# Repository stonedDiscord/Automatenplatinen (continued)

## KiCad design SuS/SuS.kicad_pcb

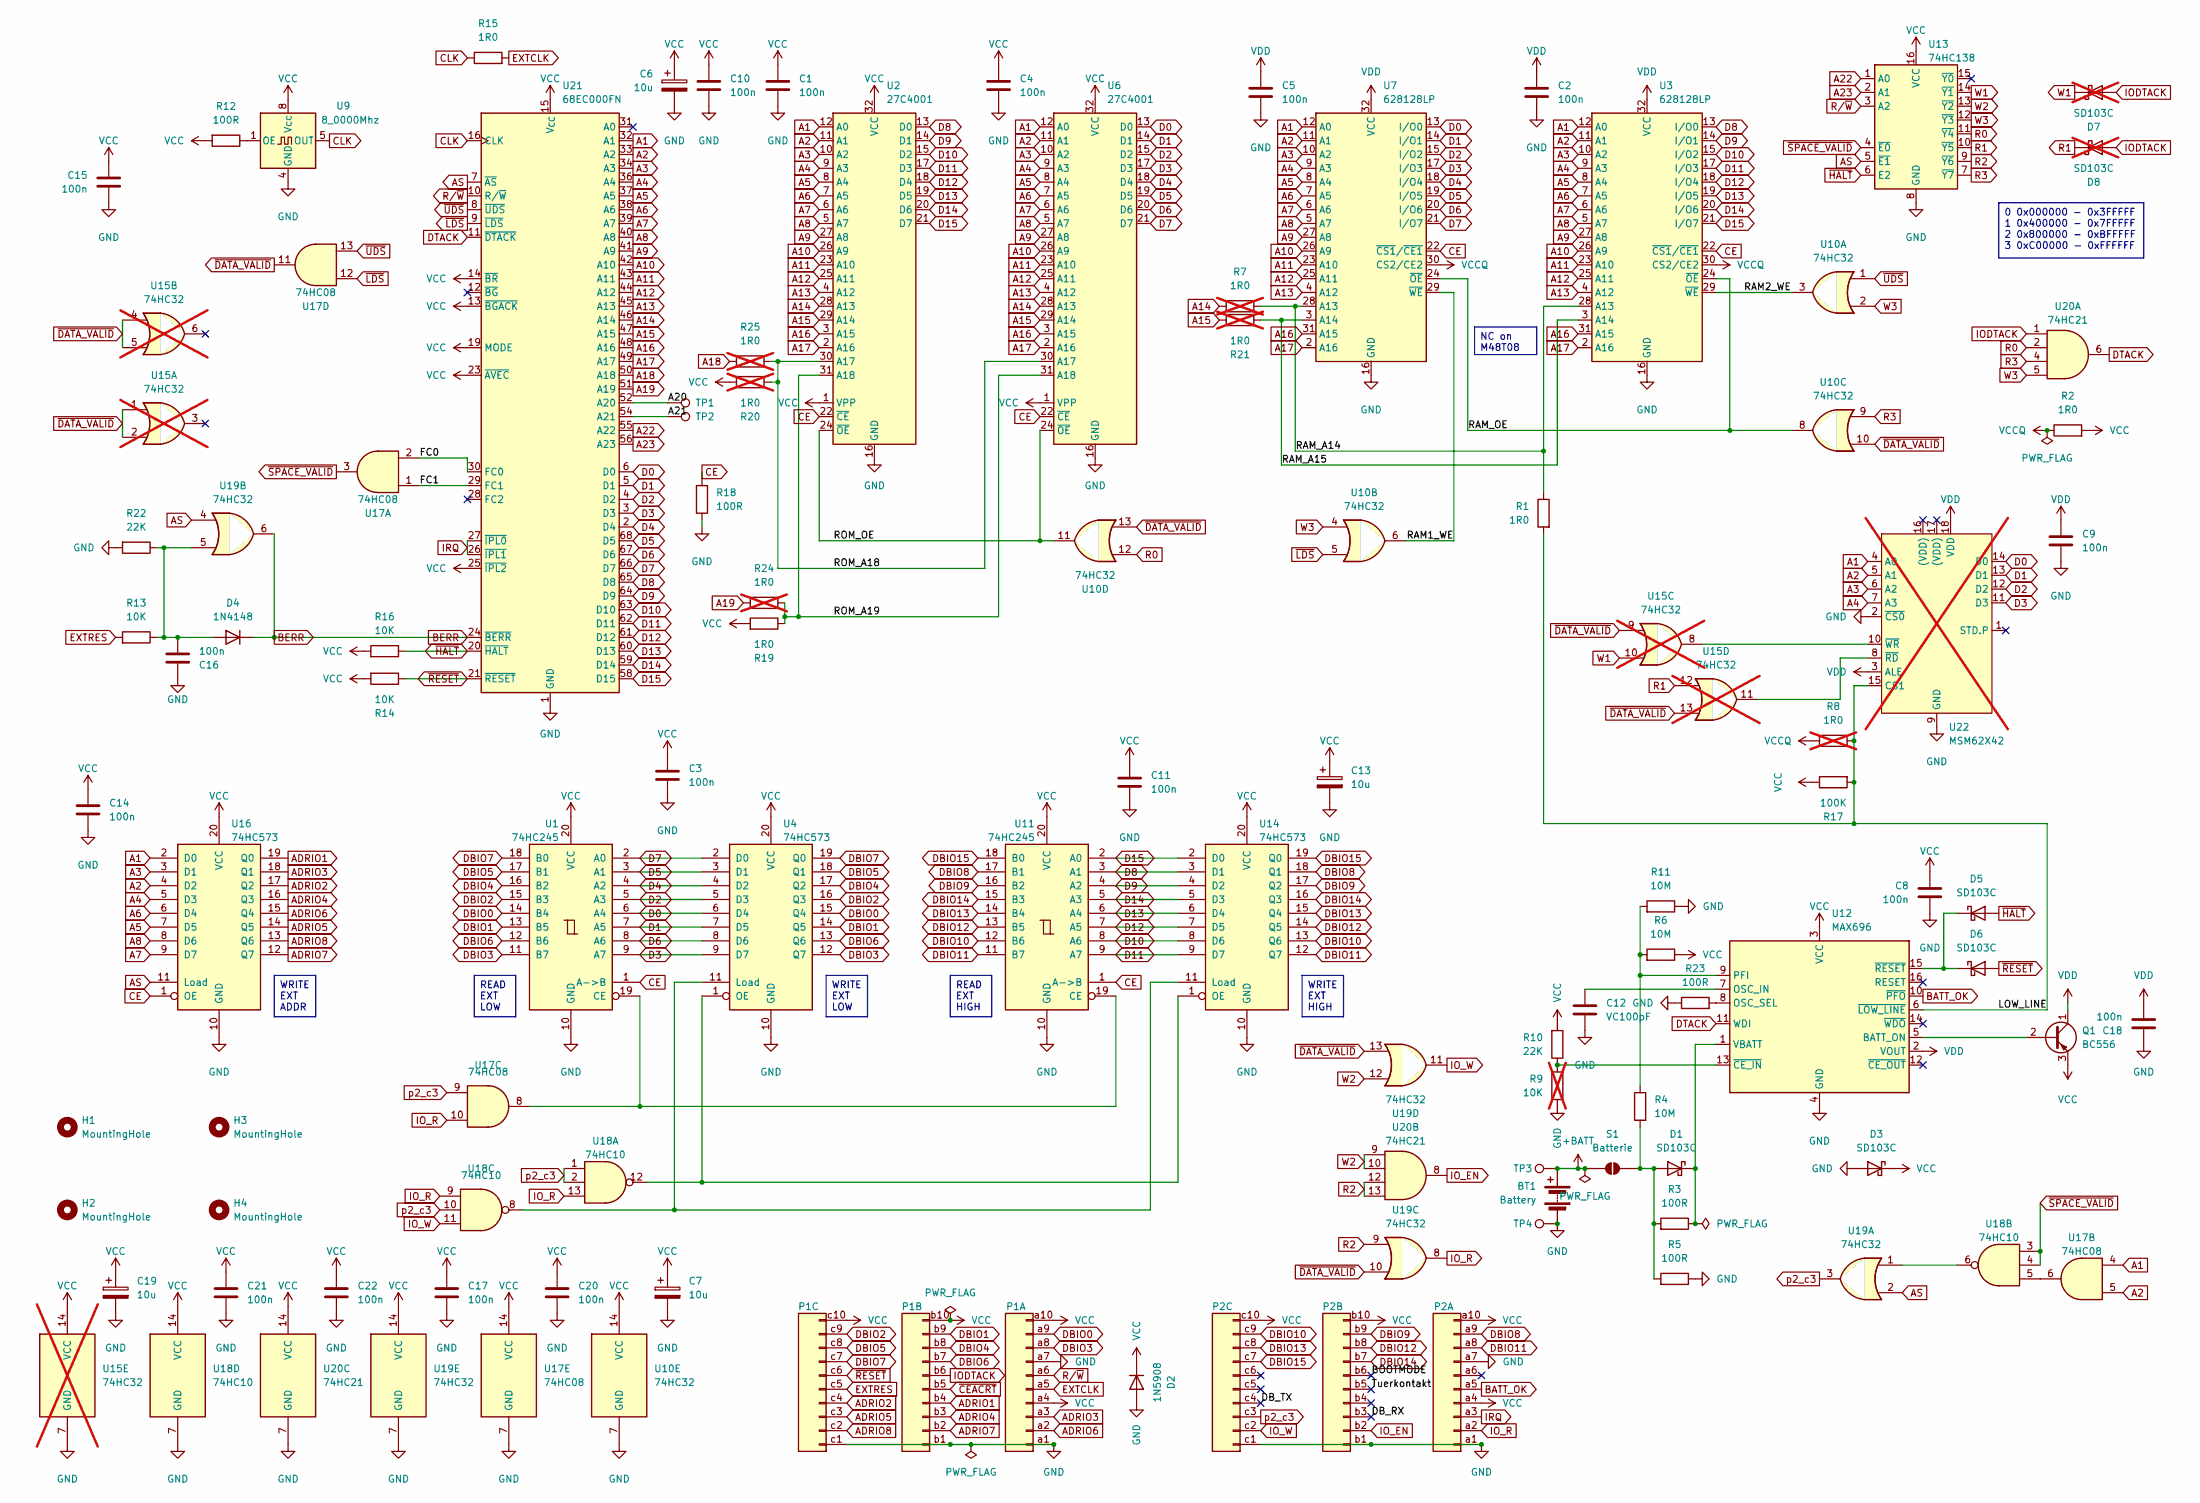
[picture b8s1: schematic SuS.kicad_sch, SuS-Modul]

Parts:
BT1: Battery; REPM1000
C1, C2, C3, C4, C5, C8, C9, C10, C11, C14, C15, C16, C17, C18, C20, C21, C22: 100n; C_Axial_L3.8mm_D2.6mm_P7.50mm_Horizontal
C6, C7, C13, C19: 10u; CP_Radial_Tantal_D5.0mm_P2.50mm
C12: VC100pF; C_Axial_L3.8mm_D2.6mm_P7.50mm_Horizontal
D1, D3, D5, D6: SD103C; D_DO-34_SOD68_P7.62mm_Horizontal
D2: 1N5908; D_DO-27_P15.24mm_Horizontal
D4: 1N4148; D_DO-35_SOD27_P7.62mm_Horizontal
D7, D8: SD103C; D_DO-34_SOD68_P7.62mm_Horizontal; not fitted
H1, H2: MountingHole; MountingHole_3mm
H3, H4: MountingHole; MountingHole_2.1mm
P1, P2: DIN41612_03x10_ABC; DIN41612_R3_3x10_Male_Vertical_THT
Q1: BC556; TO-92
R1, R2, R15, R19: 1R0; R_Axial_DIN0207_L6.3mm_D2.5mm_P10.16mm_Horizontal
R3, R5, R12, R18, R23: 100R; R_Axial_DIN0207_L6.3mm_D2.5mm_P10.16mm_Horizontal
R4, R6, R11: 10M; R_Axial_DIN0207_L6.3mm_D2.5mm_P10.16mm_Horizontal
R7, R8, R20, R21, R24, R25: 1R0; R_Axial_DIN0207_L6.3mm_D2.5mm_P10.16mm_Horizontal; not fitted
R9: 10K; R_Axial_DIN0207_L6.3mm_D2.5mm_P10.16mm_Horizontal; not fitted
R10, R22: 22K; R_Axial_DIN0207_L6.3mm_D2.5mm_P10.16mm_Horizontal
R13, R14, R16: 10K; R_Axial_DIN0207_L6.3mm_D2.5mm_P10.16mm_Horizontal
R17: 100K; R_Axial_DIN0207_L6.3mm_D2.5mm_P10.16mm_Horizontal
S1: Batterie; SolderJumper-2_P1.3mm_Open_Pad1.0x1.5mm
TP1, TP2: TestPoint; TestPoint_THTPad_D1.0mm_Drill0.5mm
TP3, TP4: TestPoint; TestPoint_THTPad_D2.0mm_Drill1.0mm
U1, U11: 74HC245; DIP-20_W7.62mm
U2, U6: 27C4001; DIP-32_W15.24mm_Socket
U3, U7: 628128LP; DIP-32_W15.24mm
U4, U14, U16: 74HC573; DIP-20_W7.62mm
U9: 8_0000Mhz; Oscillator_SeikoEpson_SG-8002DC
U10, U19: 74HC32; DIP-14_W7.62mm
U12: MAX696; DIP-16_W7.62mm
U13: 74HC138; DIP-16_W7.62mm
U15: 74HC32; DIP-14_W7.62mm; not fitted
U17: 74HC08; DIP-14_W7.62mm
U18: 74HC10; DIP-14_W7.62mm
U20: 74HC21; DIP-14_W7.62mm
U21: 68EC000FN; PLCC-68_THT-Socket
U22: MSM62X42; DIP-18_W7.62mm; not fitted

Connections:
+BATT: BT1.1 (+), S1.2 (B), TP3.1 (1_1)
/A20: TP1.1 (1_1), U21.52 (A20)
/A21: TP2.1 (1_1), U21.54 (A21)
/BOOTMODE: P2.b6
/DB_RX: P2.b3
/DB_TX: P2.c4
/FC0: U17.2, U21.30 (FC0)
/FC1: U17.1, U21.29 (FC1)
/LOW_LINE: R1.2, R8.1, R17.2, U12.6 (~LOW_LINE), U22.15 (CS1)
/RAM1_WE: U7.29 (~WE), U10.6
/RAM2_WE: U3.29 (~WE), U10.3
/RAM_A14: R1.1, R7.2, U3.28 (A13), U7.28 (A13)
/RAM_A15: R21.2, U3.3 (A14), U7.3 (A14)
/RAM_OE: U3.24 (~OE), U7.24 (~OE), U10.8
/ROM_A18: R20.1, R25.2, U2.30 (A17), U6.30 (A17)
/ROM_A19: R19.1, R24.2, U2.31 (A18), U6.31 (A18)
/ROM_OE: U2.24 (~OE), U6.24 (~OE), U10.11
/Tuerkontakt: P2.b5
A1: U2.12 (A0), U3.12 (A0), U6.12 (A0), U7.12 (A0), U16.2 (D0), U17.4, U21.32 (A1), U22.4 (A0)
A2: U2.11 (A1), U3.11 (A1), U6.11 (A1), U7.11 (A1), U16.4 (D2), U17.5, U21.33 (A2), U22.5 (A1)
A3: U2.10 (A2), U3.10 (A2), U6.10 (A2), U7.10 (A2), U16.3 (D1), U21.34 (A3), U22.6 (A2)
A4: U2.9 (A3), U3.9 (A3), U6.9 (A3), U7.9 (A3), U16.5 (D3), U21.36 (A4), U22.7 (A3)
A5: U2.8 (A4), U3.8 (A4), U6.8 (A4), U7.8 (A4), U16.7 (D5), U21.37 (A5)
A6: U2.7 (A5), U3.7 (A5), U6.7 (A5), U7.7 (A5), U16.6 (D4), U21.38 (A6)
A7: U2.6 (A6), U3.6 (A6), U6.6 (A6), U7.6 (A6), U16.9 (D7), U21.39 (A7)
A8: U2.5 (A7), U3.5 (A7), U6.5 (A7), U7.5 (A7), U16.8 (D6), U21.40 (A8)
A9: U2.27 (A8), U3.27 (A8), U6.27 (A8), U7.27 (A8), U21.41 (A9)
A10: U2.26 (A9), U3.26 (A9), U6.26 (A9), U7.26 (A9), U21.42 (A10)
A11: U2.23 (A10), U3.23 (A10), U6.23 (A10), U7.23 (A10), U21.43 (A11)
A12: U2.25 (A11), U3.25 (A11), U6.25 (A11), U7.25 (A11), U21.44 (A12)
A13: U2.4 (A12), U3.4 (A12), U6.4 (A12), U7.4 (A12), U21.45 (A13)
A14: R7.1, U2.28 (A13), U6.28 (A13), U21.46 (A14)
A15: R21.1, U2.29 (A14), U6.29 (A14), U21.47 (A15)
A16: U2.3 (A15), U3.31 (A15), U6.3 (A15), U7.31 (A15), U21.48 (A16)
A17: U2.2 (A16), U3.2 (A16), U6.2 (A16), U7.2 (A16), U21.49 (A17)
A18: R25.1, U21.50 (A18)
A19: R24.1, U21.51 (A19)
A22: U13.1 (A0), U21.55 (A22)
A23: U13.2 (A1), U21.56 (A23)
ADRIO1: P1.b4, U16.19 (Q0)
ADRIO2: P1.c4, U16.17 (Q2)
ADRIO3: P1.a3, U16.18 (Q1)
ADRIO4: P1.b3, U16.16 (Q3)
ADRIO5: P1.c3, U16.14 (Q5)
ADRIO6: P1.a2, U16.15 (Q4)
ADRIO7: P1.b2, U16.12 (Q7)
ADRIO8: P1.c2, U16.13 (Q6)
AS: U13.5 (~E1), U16.11 (Load), U19.2, U19.4, U21.7 (~AS)
BATT_OK: P2.a5, U12.10 (~PFO)
BERR: D4.1 (K), U19.6, U21.24 (~BERR)
CE: R18.2, U1.1 (A->B), U2.22 (~CE), U3.22 (~CS1/~CE1), U6.22 (~CE), U7.22 (~CS1/~CE1), U11.1 (A->B), U16.1 (OE)
CLK: R15.1, U9.5 (OUT), U21.16 (CLK)
CLOCKOUT: P1.a5, R15.2
D0: U1.6 (A4), U4.6 (D4), U6.13 (D0), U7.13 (I/O0), U21.6 (D0), U22.14 (D0)
D1: U1.7 (A5), U4.7 (D5), U6.14 (D1), U7.14 (I/O1), U21.5 (D1), U22.13 (D1)
D2: U1.5 (A3), U4.5 (D3), U6.15 (D2), U7.15 (I/O2), U21.4 (D2), U22.12 (D2)
D3: U1.9 (A7), U4.9 (D7), U6.17 (D3), U7.17 (I/O3), U21.3 (D3), U22.11 (D3)
D4: U1.4 (A2), U4.4 (D2), U6.18 (D4), U7.18 (I/O4), U21.2 (D4)
D5: U1.3 (A1), U4.3 (D1), U6.19 (D5), U7.19 (I/O5), U21.68 (D5)
D6: U1.8 (A6), U4.8 (D6), U6.20 (D6), U7.20 (I/O6), U21.67 (D6)
D7: U1.2 (A0), U4.2 (D0), U6.21 (D7), U7.21 (I/O7), U21.66 (D7)
D8: U2.13 (D0), U3.13 (I/O0), U11.3 (A1), U14.3 (D1), U21.65 (D8)
D9: U2.14 (D1), U3.14 (I/O1), U11.4 (A2), U14.4 (D2), U21.64 (D9)
D10: U2.15 (D2), U3.15 (I/O2), U11.8 (A6), U14.8 (D6), U21.63 (D10)
D11: U2.17 (D3), U3.17 (I/O3), U11.9 (A7), U14.9 (D7), U21.62 (D11)
D12: U2.18 (D4), U3.18 (I/O4), U11.7 (A5), U14.7 (D5), U21.61 (D12)
D13: U2.19 (D5), U3.19 (I/O5), U11.6 (A4), U14.6 (D4), U21.60 (D13)
D14: U2.20 (D6), U3.20 (I/O6), U11.5 (A3), U14.5 (D3), U21.59 (D14)
D15: U2.21 (D7), U3.21 (I/O7), U11.2 (A0), U14.2 (D0), U21.58 (D15)
DBIO0: P1.a9, U1.14 (B4), U4.15 (Q4)
DBIO1: P1.b9, U1.13 (B5), U4.14 (Q5)
DBIO2: P1.c9, U1.15 (B3), U4.16 (Q3)
DBIO3: P1.a8, U1.11 (B7), U4.12 (Q7)
DBIO4: P1.b8, U1.16 (B2), U4.17 (Q2)
DBIO5: P1.c8, U1.17 (B1), U4.18 (Q1)
DBIO6: P1.b7, U1.12 (B6), U4.13 (Q6)
DBIO7: P1.c7, U1.18 (B0), U4.19 (Q0)
DBIO8: P2.a9, U11.17 (B1), U14.18 (Q1)
DBIO9: P2.b9, U11.16 (B2), U14.17 (Q2)
DBIO10: P2.c9, U11.12 (B6), U14.13 (Q6)
DBIO11: P2.a8, U11.11 (B7), U14.12 (Q7)
DBIO12: P2.b8, U11.13 (B5), U14.14 (Q5)
DBIO13: P2.c8, U11.14 (B4), U14.15 (Q4)
DBIO14: P2.b7, U11.15 (B3), U14.16 (Q3)
DBIO15: P2.c7, U11.18 (B0), U14.19 (Q0)
DTACK: U12.11 (WDI), U20.6, U21.11 (~DTACK)
GND: BT1.2 (-), C1.2, C2.2, C3.2, C4.2, C5.2, C6.2, C7.2, C8.2, C9.2, C10.2, C11.2, C12.2, C13.2, C14.2, C15.2, C16.1, C17.2, C18.1, C19.2, C20.2, C21.2, C22.2, D2.2 (A), D3.2 (A), P1.a1, P1.a7, P1.b1, P1.c1, P2.a1, P2.a7, P2.b1, P2.c1, R5.1, R9.1, R11.1, R18.1, R22.2, R23.1, TP4.1 (1_1), U1.10 (GND), U2.16 (GND), U3.16 (GND), U4.10 (GND), U6.16 (GND), U7.16 (GND), U9.4 (GND), U10.7 (GND), U11.10 (GND), U12.4 (GND), U13.8 (GND), U14.10 (GND), U15.7 (GND), U16.10 (GND), U17.7 (GND), U18.7 (GND), U19.7 (GND), U20.7 (GND), U21.1 (GND), U21.17 (GND), U21.18 (GND), U21.35 (GND), U21.57 (GND), U22.2 (~CS0), U22.9 (GND)
IO_EN: P2.b2, U20.8
IO_R: P2.a2, U17.10, U18.9, U18.13, U19.8
IO_W: P2.c2, U18.11, U19.11
IRQ: P2.a3, U21.26 (~IPL1), U21.27 (~IPL0)
unnamed: D1.2 (A), R3.2, R4.2, R5.2, S1.1 (A)
unnamed: D1.1 (K), R3.1, U12.1 (VBATT)
unnamed: C16.2, D4.2 (A), R13.1, R22.1, U19.5
unnamed: D5.1 (K), D6.1 (K), U12.15 (~RESET)
unnamed: Q1.2 (B), U12.5 (BATT_ON)
unnamed: U1.19 (CE), U11.19 (CE), U17.8
unnamed: R12.1, U9.1 (OE)
unnamed: C12.1, U12.7 (OSC_IN)
unnamed: R23.2, U12.8 (OSC_SEL)
unnamed: R4.1, R6.2, R11.2, U12.9 (PFI)
unnamed: R9.2, R10.1, U12.13 (~CE_IN)
unnamed: U4.11 (Load), U14.11 (Load), U18.8
unnamed: U4.1 (OE), U14.1 (OE), U18.12
unnamed: U17.6, U18.5
unnamed: U18.6, U19.1
unnamed: U15.11, U22.8 (~RD)
unnamed: U15.8, U22.10 (~WR)
R0: U10.12, U13.11 (~Y4), U20.2
R1: D8.1 (K), U13.10 (~Y5), U15.12
R2: U13.9 (~Y6), U19.9, U20.12, U20.13
R3: U10.9, U13.7 (~Y7), U20.4
R/~W: P1.a6, U13.3 (A2), U21.10 (R/~W)
VCC: C1.1, C3.1, C4.1, C6.1, C7.1, C8.1, C10.1, C11.1, C13.1, C14.1, C15.1, C17.1, C19.1, C20.1, C21.1, C22.1, D2.1 (K), D3.1 (K), P1.a4, P1.a10, P1.b10, P1.c10, P2.a4, P2.a10, P2.b10, P2.c10, Q1.3 (E), R2.2, R6.1, R10.2, R12.2, R14.2, R16.2, R17.1, R19.2, R20.2, U1.20 (VCC), U2.1 (VPP), U2.32 (VCC), U4.20 (VCC), U6.1 (VPP), U6.32 (VCC), U9.8 (Vcc), U10.14 (VCC), U11.20 (VCC), U12.3 (VCC), U13.16 (VCC), U14.20 (VCC), U15.14 (VCC), U16.20 (VCC), U17.14 (VCC), U18.14 (VCC), U19.14 (VCC), U20.14 (VCC), U21.13 (~BGACK), U21.14 (~BR), U21.15 (V_{CC}), U21.19 (MODE), U21.23 (~AVEC), U21.25 (~IPL2), U21.53 (V_{CC})
VCCQ: R2.1, R8.2, U3.30 (CS2/CE2), U7.30 (CS2/CE2)
VDD: C2.1, C5.1, C9.1, C18.2, Q1.1 (C), U3.32 (VCC), U7.32 (VCC), U12.2 (VOUT), U22.3 (ALE), U22.18 (VDD)
W1: D7.1 (K), U13.14 (~Y1), U15.10
W2: U13.13 (~Y2), U19.12, U20.9, U20.10
W3: U10.2, U10.4, U13.12 (~Y3), U20.5
cBERR: P1.c5, R13.2
p1_b6: D7.2 (A), D8.2 (A), P1.b6, U20.1
p2_c3: P2.c3, U17.9, U18.1, U18.2, U18.10, U19.3
~DATA_VALID: U10.10, U10.13, U15.1, U15.2, U15.4, U15.5, U15.9, U15.13, U17.11, U19.10, U19.13
~HALT: D5.2 (A), R16.1, U13.6 (E2), U21.20 (~HALT)
~LDS: U10.5, U17.12, U21.9 (~LDS)
~RESET: D6.2 (A), P1.c6, R14.1, U21.21 (~RESET)
~SPACE_VALID: U13.4 (~E0), U17.3, U18.3, U18.4
~UDS: U10.1, U17.13, U21.8 (~UDS)

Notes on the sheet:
0 0x000000 - 0x3FFFFF 1 0x400000 - 0x7FFFFF 2 0x800000 - 0xBFFFFF 3 0xC00000 - 0xFFFFFF
WRITE EXT LOW
WRITE EXT HIGH
READ EXT LOW
WRITE EXT ADDR
NC on M48T08
READ EXT HIGH

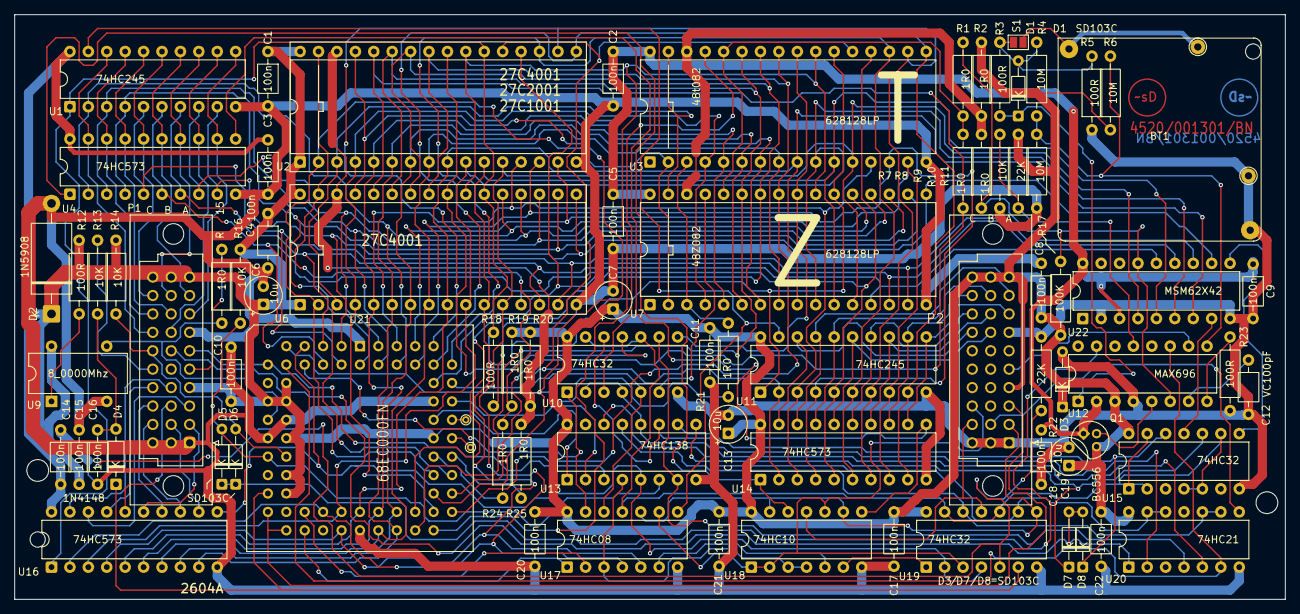
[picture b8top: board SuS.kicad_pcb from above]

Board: 2 copper layers, 175.3 x 80.6 mm, 88 parts (0 on the bottom side), 124 nets.

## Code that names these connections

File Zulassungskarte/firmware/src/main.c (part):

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
// --- Configuration ---

#define MOSI_PIN PB3
#define MISO_PIN PB4
#define SCK_PIN  PB5

// Command codes received from SPI Master
enum Command {
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// --- Crypto Operations ---

static uint8_t transform_byte_a(uint8_t val) {
    uint8_t res = 0;
    uint8_t mask = 0x25;
    for (uint8_t i = 0; i < 8; i++) {
        res <<= 1;
        if (mask & 0x80) res += val;
        mask <<= 1;
    }
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}

static uint8_t transform_byte_b(uint8_t val) {
    uint8_t res = 0;
    uint8_t mask = 0xAD;
    for (uint8_t i = 0; i < 8; i++) {
        res <<= 1;
        if (mask & 0x80) res += val;
        mask <<= 1;
    }
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    PORTD = 0;
    PORTC = 0;
    PORTB = 0;
    DDRB = 0xF7; // PB3 (MOSI) as input, others as output

    // Watchdog Setup
    WDTCSR |= (1 << WDCE) | (1 << WDE);
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
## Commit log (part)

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2025-02-08 plcc68
2025-02-19 stecker korrigiert
2025-03-09 werte
2025-03-11 cap werte
2025-03-13 ausles
2025-03-13 lampe
2025-03-13 taster
2025-03-13 pins
2025-03-13 taster LED
2025-03-13 zlk alt
2025-03-14 silkscreen, parts
2025-03-14 rueckseite maske
2025-03-14 aussparung
2025-03-14 cleanup
2025-03-14 arduino isp und anschluss der normal am halter ist
2025-03-15 fehler weg
2025-03-17 st25 tastatur
2025-03-17 nsm adapterplatine unterseite
2025-03-18 5v und loecher
2025-03-18 kleinerer sim kontakt
2025-03-19 komplett? muss ich noch pruefen
2025-03-19 bally hat die kontakte anders rum
2025-03-20 led und ffc
2025-03-20 loecher dann doch
2025-03-20 eckendeckel
2025-03-20 deckel sonne
2025-03-20 beschriftung hinten
2025-03-21 halbzeit
2025-03-22 rev1
2025-03-23 zweite reihe
2025-03-23 stromleitungen
2025-03-23 beschriftung
2025-03-24 st25 tastatur gerber
2025-03-25 kicad 9 update
2025-03-25 DATENBANK
2025-03-25 loch
2025-03-26 klassik
2025-03-26 direkt adapter
2025-03-28 kicad9 update
2025-03-29 gleichrichter
2025-03-29 kleine lampe
2025-03-29 taster gerber
2025-03-29 halter gerber
2025-03-30 jumper
2025-04-01 programmierboard bis auf 2 linien
2025-04-01 vnd10bsp
2025-04-02 gehäuse schrott
2025-04-02 emp mit foto
2025-04-03 schalplan
2025-04-03 export
2025-04-03 noch eine tastatur
2025-04-03 schaltplan
2025-04-07 vias
2025-04-10 widerstand
2025-04-10 more buttons
2025-04-10 power
2025-04-10 inner
2025-04-11 stifte nach vorne wegen dem hebel
2025-04-15 12v zlk
2025-04-24 spannungs messung
2025-04-29 language tag
2025-04-29 kontaktinfos
2025-04-29 bilder raus
2025-04-29 zlk widerstand
2025-04-29 rumgeschiebe
2025-05-02 sprache
2025-05-02 drecks plugin
2025-05-05 rechtschreibung
2025-05-05 formulierung
2025-05-05 spannung aus dem kopf
2025-05-06 station text
2025-05-07 triple16
2025-05-08 ausgabe von 3d
2025-05-08 roentgen
2025-05-09 unterseite scan
2025-05-13 bilder weg
2025-05-13 kondensatoren
2025-05-13 text verschoben
2025-05-19 funnyled
2025-06-03 usbasp stecker
2025-06-04 komponenten werte
2025-06-06 kondensator fehlte
2025-06-07 oberseite
2025-06-09 ZLK software
2025-06-09 eeprom
2025-06-09 autodetect cpu
2025-06-16 25.2
2025-06-16 halbe miete
2025-06-24 xray
2025-06-24 no renders
2025-06-24 step files are copyright manufacturer
2025-06-24 chinaknopf
2025-06-26 testp
2025-06-28 aussen pins
2025-06-28 no more autodetect (didnt work)
2025-06-28 wieso war das da
2025-06-29 linie
2025-07-03 soundregler
2025-07-09 lampentreiber
2025-07-09 seite 1
2025-07-12 lampen
2025-07-12 vorcpu
2025-07-12 ncpu
2025-07-12 schlimmer wie vorher
2025-07-12 mode
2025-07-13 unterseite durch
2025-07-13 modul
2025-07-13 adapter
2025-07-13 modul2
2025-07-21 oben
2025-07-24 bw bilder
2025-07-24 modul atmega
2025-07-25 systemmodul fertig
2025-07-31 pin2
2025-08-08 fotos
2025-08-08 lumberg stecker
2025-08-11 hinweis lol
2025-08-16 einladung
2025-08-18 gitignore
2025-08-18 render
2025-08-20 knopf
2025-09-10 lamp refresh
2025-09-11 loader
2025-09-15 fidu
2025-09-16 led widerstand
2025-09-17 scan
2025-09-21 daten
2025-10-03 kran
2025-11-07 weg mit dem zeug
2025-11-28 512k
2025-11-29 systemmodul reset
2025-11-29 move board
2025-11-29 reset typ
2025-11-29 teilenummern
2025-12-06 tastatur adapter
2025-12-06 dicke fertig
2025-12-06 oki du ar
2025-12-06 gl label und q
2025-12-06 diode
2025-12-06 kompletti
2025-12-15 4017 beschriftung
2026-01-02 sussy
2026-01-02 move symbols
2026-01-02 epson rtc
2026-01-02 uPD70325
2026-01-02 move 2
2026-01-02 replies
2026-01-02 anleitung
2026-01-05 build script
2026-01-05 clown emoji
2026-01-05 init boot loader
2026-01-08 modclk
2026-01-09 bgnd
2026-01-14 neues bild
2026-01-17 greeeen
2026-01-20 3d export
2026-01-20 3d halter
2026-02-01 ste25
2026-02-11 net namen
2026-02-11 cpu und eprom
2026-02-11 lib table
2026-02-11 kleinigkeit
2026-02-11 nsm jumper
2026-02-11 zlk tag connect
2026-02-11 del alt
2026-02-11 untenrum fertig
2026-02-11 alles verbunden
2026-02-12 battok
2026-02-12 silkscreen
2026-02-16 bild
2026-02-16 onboard rom
2026-02-26 command
2026-02-26 connector
2026-02-26 display
2026-02-26 no error
2026-03-07 sus pins
2026-03-07 jamma adapter
2026-03-07 druckerport
2026-03-20 Create erc-drc.yml
    test
2026-03-20 1stern
2026-03-20 project matrix
2026-03-20 no fail fast
2026-03-20 report file
2026-03-20 list
2026-03-20 Kompakt
2026-03-20 fix jason
2026-03-20 archive is new
2026-03-20 either
2026-03-20 files instead
2026-03-20 names
2026-03-20 still run drc
2026-03-20 paths
2026-03-20 module
2026-03-20 step summary instead of artifact
2026-03-20 stop spam
2026-03-20 html tags
2026-03-21 ercdrc
2026-03-21 erc lamp
2026-03-21 war eh falsch
2026-03-21 zlk drc
2026-03-21 silk
2026-03-30 sus testpoint
2026-04-01 alt pins
2026-04-01 kicad 10
2026-04-01 match
2026-04-01 erc+drc
2026-04-02 sudo Update erc-drc.yml
2026-04-02 too good to be true
2026-04-02 print summary
2026-04-02 simpler
2026-04-02 500mb difference but comes with symbols
2026-04-02 global libraries
2026-04-02 theres no place like $HOME
2026-04-04 kicad 10 update
2026-04-04 finish board
2026-04-06 alles raus
2026-04-06 debugstation
2026-04-06 renata
2026-04-06 LEDs andersrum
2026-04-11 atmel test
2026-04-11 jamma pcb
2026-04-12 kicad10
2026-04-13 ende drucker und jamma unten
2026-04-13 sys25 erc
2026-04-13 batterie courtyard
2026-04-16 attempt
2026-04-17 gehäuse notiz
2026-04-17 anderes
2026-04-22 lader
2026-04-23 88pa
2026-04-24 lader bestellt
2026-04-24 station verkleinert
2026-04-26 move to header
2026-04-26 timers
2026-04-26 autoformat
2026-04-26 move rtc
2026-04-26 rename
2026-04-26 move addresses
2026-04-28 isp adapter
2026-04-28 zlk fw
2026-04-29 refactor
2026-04-29 rename to c
2026-04-29 ym oben
2026-04-29 spi command
2026-05-03 ele bom
2026-05-03 export script
2026-05-03 atmega order
2026-05-03 extra defines
2026-05-07 ym pins
2026-05-11 diagram
2026-05-11 fix footprints
2026-05-11 3d model and gnd fill top right
2026-05-11 warnings
2026-05-11 isp readme
2026-05-11 move to https://github.com/stonedDiscord/ArduinoISP
2026-05-11 soundkarte symbols
2026-05-11 zlk firmware template
2026-05-13 rom line
2026-05-13 videokarte m encoder
2026-05-13 zlk pio
2026-05-13 halter sid sod
2026-05-13 zl script
2026-05-13 pio config
2026-05-13 upload script
2026-05-13 split erc and drc
2026-05-13 gnu as
2026-05-13 b script
2026-05-13 bytes
2026-05-15 chips
2026-05-19 add msm
2026-05-19 doppelt
2026-05-19 aus der doku
2026-05-19 backg/manoman
2026-05-19 signalnamen
2026-05-20 kleiner
2026-05-20 intel
2026-05-24 strom
2026-05-24 rarr
2026-05-30 plsatik
